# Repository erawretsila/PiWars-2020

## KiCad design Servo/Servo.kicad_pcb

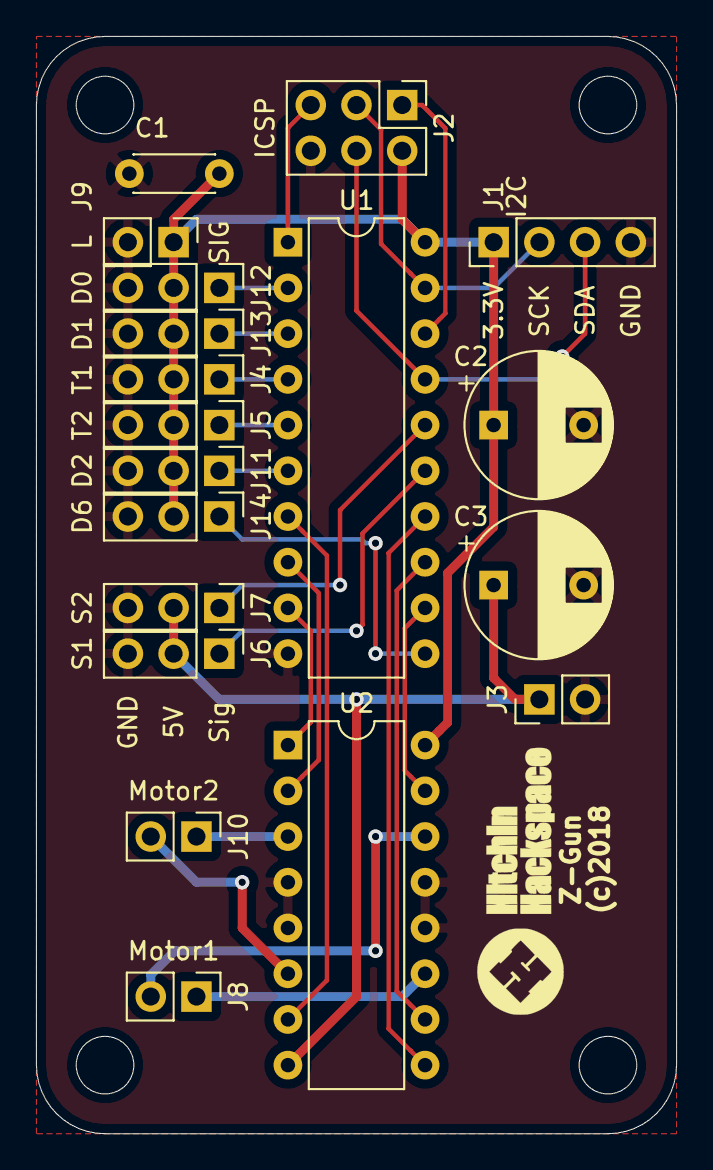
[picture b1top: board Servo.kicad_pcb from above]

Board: 2 copper layers, 35.6 x 61.0 mm, 19 parts (0 on the bottom side), 25 nets.

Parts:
C1: C; C_Disc_D4.3mm_W1.9mm_P5.00mm
C2, C3: CP; CP_Radial_D8.0mm_P5.00mm
J1: Pi; PinHeader_1x04_P2.54mm_Vertical
J2: ISP; PinHeader_2x03_P2.54mm_Vertical
J3: Power; PinHeader_1x02_P2.54mm_Vertical
J4, J5, J11, J12, J13, J14: Conn_01x03; PinHeader_1x03_P2.54mm_Vertical
J6: Servo 1; PinHeader_1x03_P2.54mm_Vertical
J7: Servo 2; PinHeader_1x03_P2.54mm_Vertical
J8: Motor1; PinHeader_1x02_P2.54mm_Vertical
J9: Laser; PinHeader_1x02_P2.54mm_Vertical
J10: Motor2; PinHeader_1x02_P2.54mm_Vertical
U1: ATtiny2313A-PU; DIP-20_W7.62mm
U2: L293D; DIP-16_W7.62mm

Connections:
+3.3VA: C1.1, C2.1, J1.1, J2.2, J4.2, J5.2, J9.1, J11.2, J12.2, J13.2, J14.2, U1.20, U2.16
D0: J12.1, U1.2
D1: J13.1, U1.3
D2: J11.1, U1.6
D6: J14.1, U1.11
GND: C1.2, C2.2, C3.2, J1.4, J2.6, J3.2, J4.3, J5.3, J6.3, J7.3, J9.2, J11.3, J12.3, J13.3, J14.3, U1.10, U2.4, U2.5, U2.12, U2.13
M1A: U1.13, U2.10
M1B: U1.12, U2.15
M1E: U1.14, U2.9
M2A: U1.8, U2.2
M2B: U1.7, U2.7
M2E: U1.9, U2.1
MISO: J2.1, U1.18
MOSI-SDA: J1.3, J2.4, U1.17
unnamed: J8.1, U2.11
unnamed: J8.2, U2.14
unnamed: J10.1, U2.3
unnamed: J10.2, U2.6
RESET: J2.5, U1.1
SCK: J1.2, J2.3, U1.19
Servo-1: J6.1, U1.15
Servo-2: J7.1, U1.16
SingleShot-1: J4.1, U1.4
SingleShot-2: J5.1, U1.5
Vdrive: C3.1, J3.1, J6.2, J7.2, U2.8

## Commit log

2019-08-09 PCB & code updated, Single shot option on both motors
2019-08-12 re-factored z-gun code for ease of migration to alternative controllers
2019-08-13 i2c slave objectcode
2019-08-13 Watchdog timer enabled
2019-08-20 re-factored code - makefile does not correctly generate eeprom file 1st line needs deleting
2019-08-21 Created Data sheet & Updated schematic
2019-08-21 doc update
2019-08-22 Makefile EEProm output corrected. Usi_i2c_Slave.h updated to support 2313a as well as 2313
2019-09-04 Cleaned code & comments
2019-09-05 Port D GPIO control + Frequency calibration
2019-10-01 improvements to i2c code
2019-10-03 ammended Watchdog to prevent I2C bus lockup
2019-10-08 corrected I2c holding clock when data for another device is placed on the bus.
2019-10-08 MAX I2c speed 350khz ???
2019-10-09 further i2c fixes
2019-10-09 Almost OK I2c - set address & read must be performed separately due to RP timing issues
2019-10-30 Added Dual Quadrature Decode in registers 0x08,0x09 & 0x0a,0x0b

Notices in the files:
Servo/Servo.kicad_pcb:
(c)2018
